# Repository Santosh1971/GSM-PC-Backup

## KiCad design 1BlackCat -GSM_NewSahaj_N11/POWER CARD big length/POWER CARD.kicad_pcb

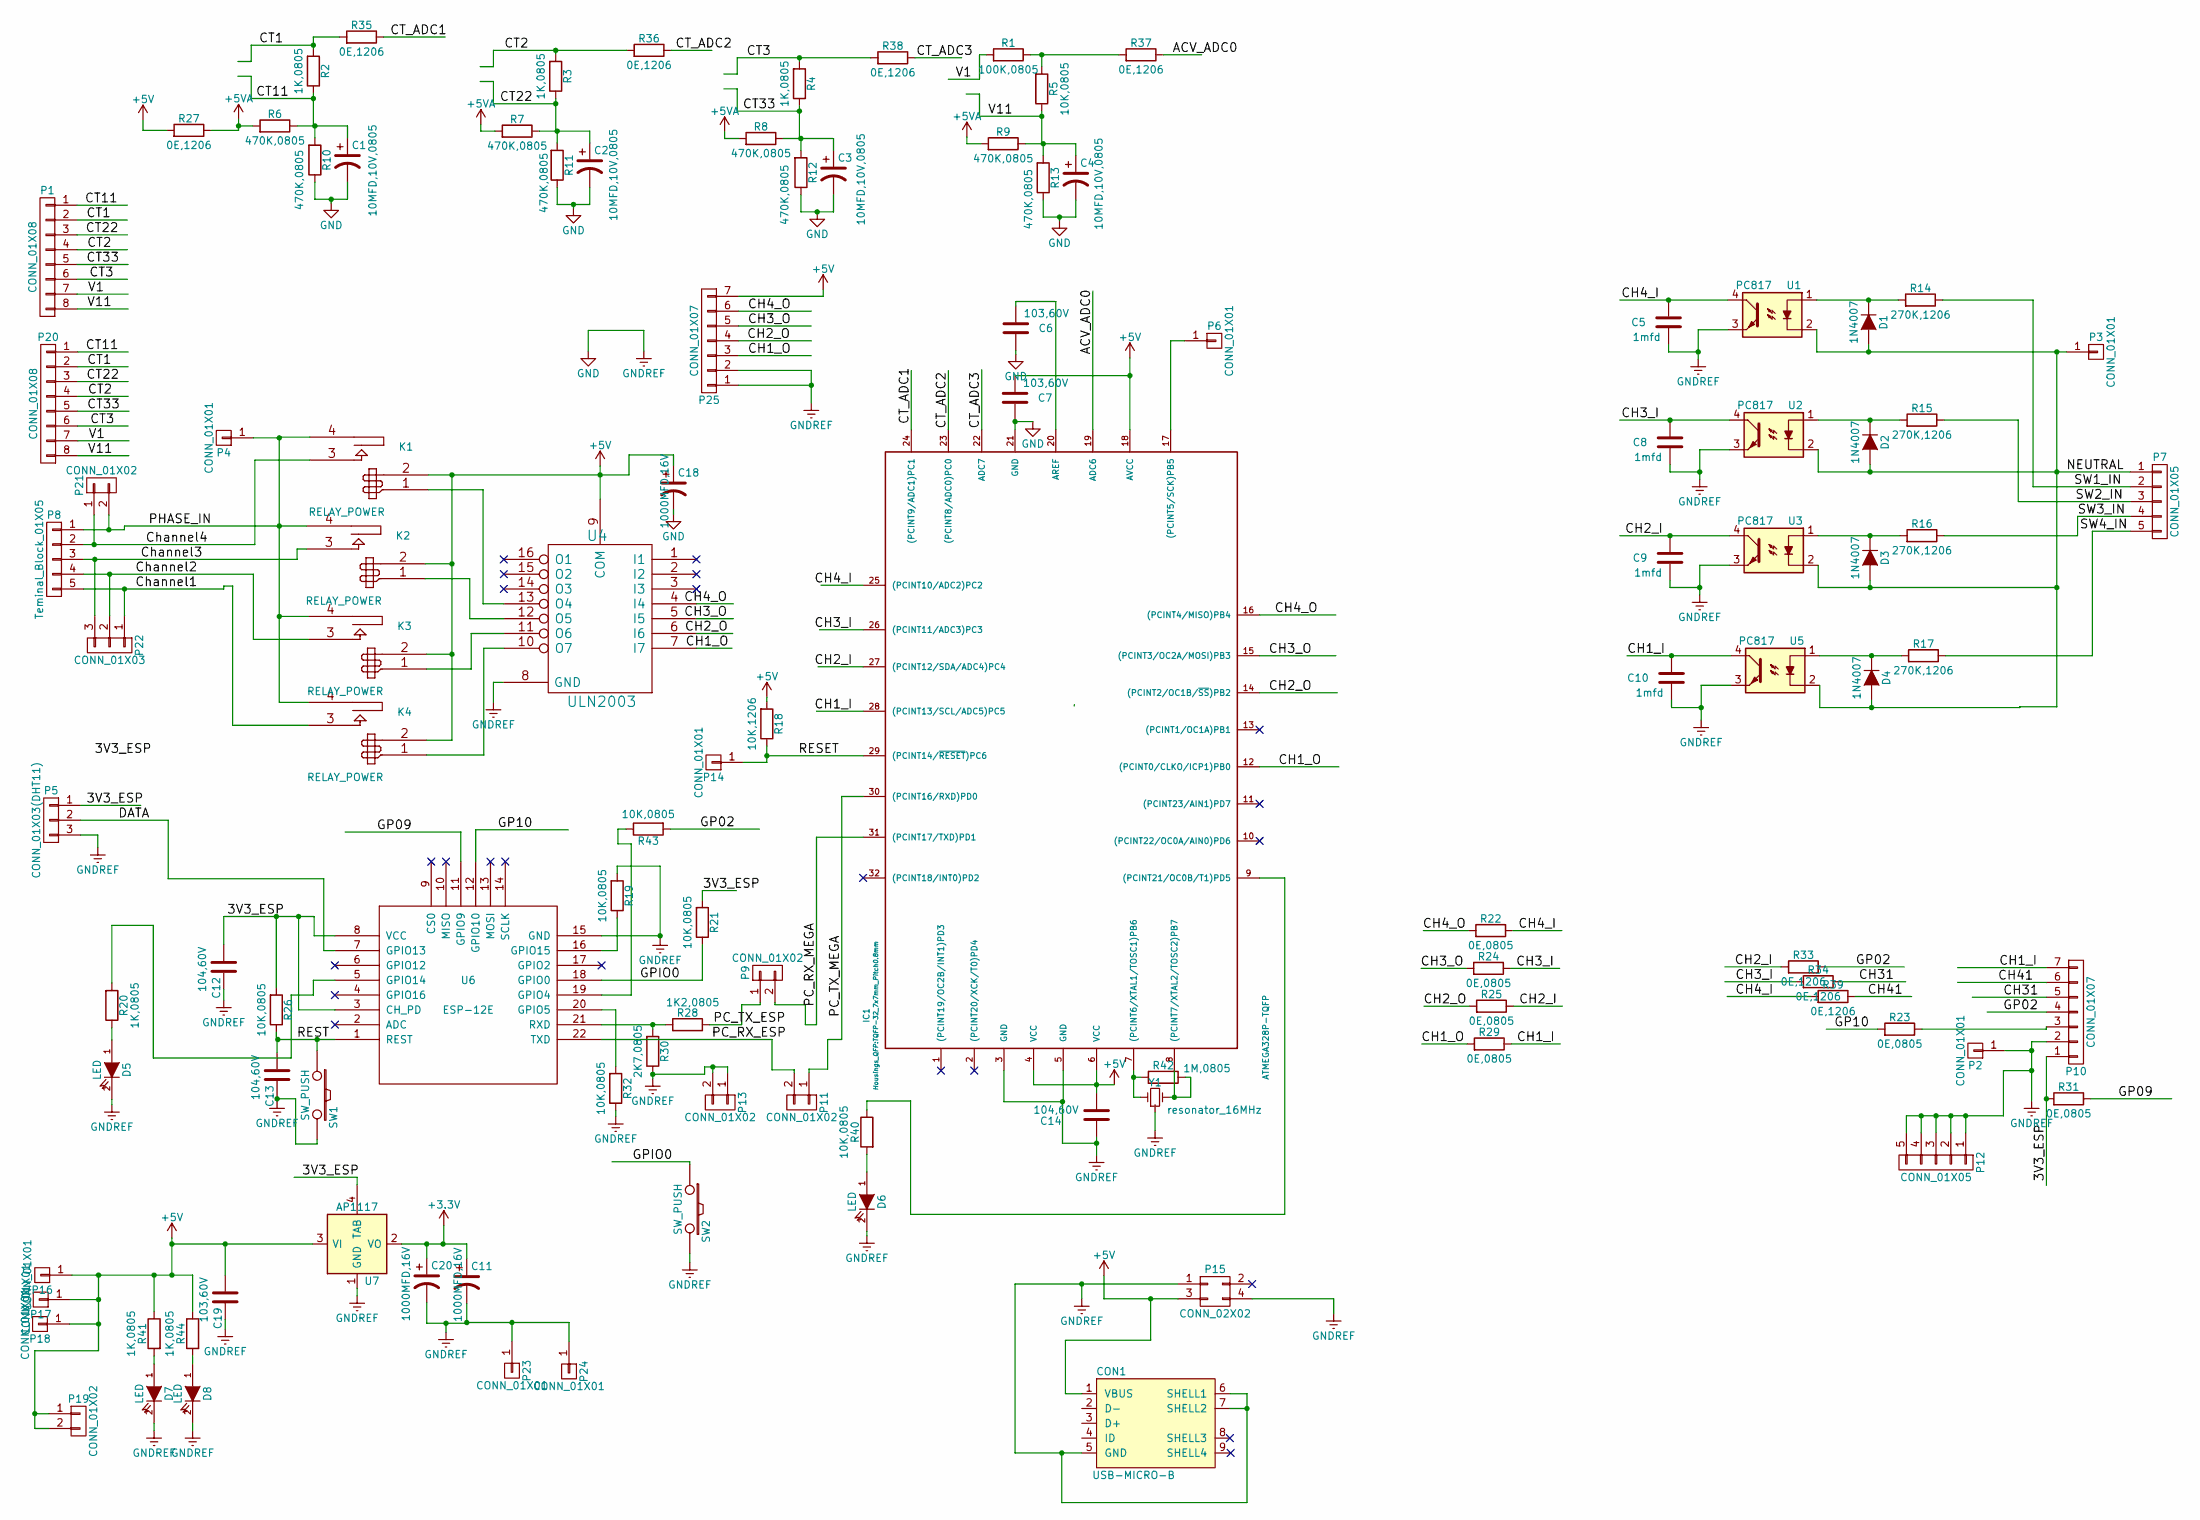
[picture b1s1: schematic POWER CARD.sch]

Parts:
C1, C2, C3, C4: 10MFD,10V,0805; C_0805
C5, C8, C9, C10: 1mfd; C_0805
C6, C19: 103,60V; C_0805
C7: 103,60V; R_0805
C11, C20: 1000MFD,16V; C_Radial_D5_L6_P2.5
C12, C13, C14: 104,60V; C_0805
C18: 1000MFD,16V; C_Radial_D8_L11.5_P3.5
CON1: USB-MICRO-B; USB_Micro-B
D1, D2, D3, D4: 1N4007; SMA_1N4007
D5, D6, D7, D8: LED; LED_0805_ok
IC1: ATMEGA328P-TQFP; TQFP-32_7x7mm_Pitch0.8mm
K1, K2, K3, K4: RELAY_POWER; Relay_KYOTA_KT-594
P1: CONN_01X08; Pin_Header_Straight_1x08
P2: CONN_01X01; Power_card_MegaSize_OK
P3, P4: CONN_01X01; Pin_Header_Straight_1x01
P5: CONN_01X03(DHT11); Pin_Header_Straight_1x03
P6, P14, P16, P17, P18, P23, P24: CONN_01X01; Pin_Header_Straight_1x01_TP_SMD
P7: CONN_01X05; TerminalBlock_WAGO-236_2Stift_RM5mm_5pol
P8: Teminal_Block_01X05; TerminalBlock_WAGO-236_2Stift_RM5mm_5pol_OK
P9, P11, P13, P19: CONN_01X02; Pin_Header_Straight_1x02
P10, P25: CONN_01X07; Pin_Header_Straight_1x07
P12: CONN_01X05; Pin_Header_Straight_1x05
P15: CONN_02X02; Pin_Header_Straight_1x04
P20: CONN_01X08; TerminalBlock_WAGO-236_2Stift_RM5mm_8pol
P21: CONN_01X02; TerminalBlock_WAGO-236_2Stift_RM5mm_2pol
P22: CONN_01X03; TerminalBlock_WAGO-236_2Stift_RM5mm_3pol
R1: 100K,0805; R_0805
R2, R3, R4, R20, R41, R44: 1K,0805; R_0805
R5, R19, R21, R26, R32, R40, R43: 10K,0805; R_0805
R6, R7, R8, R9, R10, R11, R12, R13: 470K,0805; R_0805
R14, R15, R16, R17: 270K,1206; R_1206
R18: 10K,1206; R_1206
R22, R24, R25, R29: 0E,0805; R_0603
R23, R31: 0E,0805; R_0805
R27, R33, R34, R35, R36, R37, R38, R39: 0E,1206; R_1206
R28: 1K2,0805; R_0805
R30: 2K7,0805; R_0805
R42: 1M,0805; R_0805
SW1, SW2: SW_PUSH; SW_SPST_FSMSM
U1, U2, U3, U5: PC817; DIP-4_W7.62mm
U4: ULN2003; SOIC-16_3.9x9.9mm_Pitch1.27mm
U6: ESP-12E
U7: AP1117; SOT-223
Y1: resonator_16MHz; Resonator_16MHz_arduino

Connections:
+3V3: C11.1, C20.1, U7.2 (VO)
+5V: C7.2, C14.2, C18.1, C19.2, CON1.1 (VBUS), IC1.4 (VCC), IC1.6 (VCC), IC1.18 (AVCC), K1.2, K2.2, K3.2, K4.2, P15.3, P16.1, P17.1, P18.1, P19.1, P19.2, P25.7, R18.2, R27.2, R41.1, R44.1, U4.9 (COM), U7.3 (VI); also elsewhere on the board
+5VA: R6.2, R7.2, R8.2, R9.2, R27.1
/3V3_ESP: C12.2, P5.1, P10.1, R21.2, R26.2, R31.2, U6.3 (CH_PD), U6.8 (VCC), U7.4 (TAB)
/ACV_ADC0: IC1.19 (ADC6), R37.1
/CH1_I: C10.1, IC1.28 ((PCINT13/SCL/ADC5)PC5), P10.7, R29.1, U5.4
/CH1_O: IC1.12 ((PCINT0/CLKO/ICP1)PB0), P25.3, R29.2, U4.7 (I7)
/CH2_I: C9.1, IC1.27 ((PCINT12/SDA/ADC4)PC4), R25.1, R33.2, U3.4
/CH2_O: IC1.14 ((PCINT2/OC1B/~SS~)PB2), P25.4, R25.2, U4.6 (I6)
/CH3_I: C8.1, IC1.26 ((PCINT11/ADC3)PC3), R24.1, R34.2, U2.4
/CH3_O: IC1.15 ((PCINT3/OC2A/MOSI)PB3), P25.5, R24.2, U4.5 (I5)
/CH4_I: C5.1, IC1.25 ((PCINT10/ADC2)PC2), R22.1, R39.2, U1.4
/CH4_O: IC1.16 ((PCINT4/MISO)PB4), P25.6, R22.2, U4.4 (I4)
/CH31: P10.5, R34.1
/CH41: P10.6, R39.1
/CT1: P1.2, P20.2, R2.2, R35.2
/CT2: P1.4, P20.4, R3.2, R36.2
/CT3: P1.6, P20.6, R4.2, R38.2
/CT11: C1.1, P1.1, P20.1, R2.1, R6.1, R10.2
/CT22: C2.1, P1.3, P20.3, R3.1, R7.1, R11.2
/CT33: C3.1, P1.5, P20.5, R4.1, R8.1, R12.2
/CT_ADC1: IC1.24 ((PCINT9/ADC1)PC1), R35.1
/CT_ADC2: IC1.23 ((PCINT8/ADC0)PC0), R36.1
/CT_ADC3: IC1.22 (ADC7), R38.1
/Channel1: K4.3, P8.5, P22.1; also elsewhere on the board
/Channel2: K3.3, P8.4, P22.2; also elsewhere on the board
/Channel3: K2.3, P8.3, P22.3; also elsewhere on the board
/Channel4: K1.3, P8.2, P21.1; also elsewhere on the board
/DATA: P5.2, U6.7 (GPIO13)
/GP02: P10.4, R33.1, R43.2
/GP09: R31.1, U6.11 (GPIO9)
/GP10: R23.2, U6.12 (GPIO10)
/GPIO0: R21.1, SW2.1, U6.18 (GPIO0)
/NEUTRAL: D1.1 (A), D2.1 (A), D3.1 (A), D4.1 (A), P3.1, P7.1, U1.2, U2.2, U3.2, U5.2; also elsewhere on the board
/PC_RX_ESP: P11.2, U6.22 (TXD)
/PC_RX_MEGA: IC1.31 ((PCINT17/TXD)PD1), P9.2
/PC_TX_ESP: P9.1, R28.1
/PC_TX_MEGA: IC1.30 ((PCINT16/RXD)PD0), P11.1
/PHASE_IN: K1.4, K2.4, K3.4, K4.4, P4.1, P8.1, P21.2; also elsewhere on the board
/RESET: IC1.29 ((PCINT14/~RESET~)PC6), P14.1, R18.1
/REST: C13.2, R26.1, SW1.1, U6.1 (REST)
/SW1_IN: P7.2, R14.1; also elsewhere on the board
/SW2_IN: P7.3, R15.1; also elsewhere on the board
/SW3_IN: P7.4, R16.1; also elsewhere on the board
/SW4_IN: P7.5, R17.1; also elsewhere on the board
/V1: P1.7, P20.7, R1.2
/V11: C4.1, P1.8, P20.8, R5.1, R9.1, R13.2
GNDREF: C1.2, C2.2, C3.2, C4.2, C5.2, C6.1, C7.1, C8.2, C9.2, C10.2, C11.2, C12.1, C13.1, C14.1, C18.2, C19.1, C20.2, CON1.5 (GND), CON1.6 (SHELL1), CON1.7 (SHELL2), D5.2 (K), D6.2 (K), D7.2 (K), D8.2 (K), IC1.3 (GND), IC1.5 (GND), IC1.21 (GND), P2.1, P5.3, P10.2, P12.1, P12.2, P12.3, P12.4, P12.5, P13.1, P13.2, P15.1, P15.4, P23.1, P24.1, P25.1, P25.2, R10.1, R11.1, R12.1, R13.1, R19.2, R30.1, R32.1, SW1.2, SW2.2, U1.3, U2.3, U3.3, U4.8 (GND), U5.3, U6.15 (GND), U7.1 (GND), Y1.3; also elsewhere on the board
unnamed: C6.2, IC1.20 (AREF)
unnamed: D1.2 (K), R14.2, U1.1
unnamed: D2.2 (K), R15.2, U2.1
unnamed: D3.2 (K), R16.2, U3.1
unnamed: D4.2 (K), R17.2, U5.1
unnamed 53: D5.1 (A), R20.1; also elsewhere on the board
unnamed: D6.1 (A), R40.2
unnamed: D7.1 (A), R41.2
unnamed: D8.1 (A), R44.2
unnamed: IC1.7 ((PCINT6/XTAL1/TOSC1)PB6), R42.2, Y1.1
unnamed: IC1.8 ((PCINT7/XTAL2/TOSC2)PB7), R42.1, Y1.2
unnamed: IC1.9 ((PCINT21/OC0B/T1)PD5), R40.1
unnamed: IC1.17 ((PCINT5/SCK)PB5), P6.1
unnamed: K1.1, U4.13 (O4)
unnamed: K2.1, U4.12 (O5)
unnamed: K3.1, U4.11 (O6)
unnamed: K4.1, U4.10 (O7)
unnamed: P10.3, R23.1
unnamed: R1.1, R5.2, R37.2
unnamed: R19.1, U6.16 (GPIO15)
unnamed: R20.2, U6.5 (GPIO14)
unnamed: R28.2, R30.2, U6.21 (RXD)
unnamed: R32.2, U6.20 (GPIO5)
unnamed: R43.1, U6.19 (GPIO4)

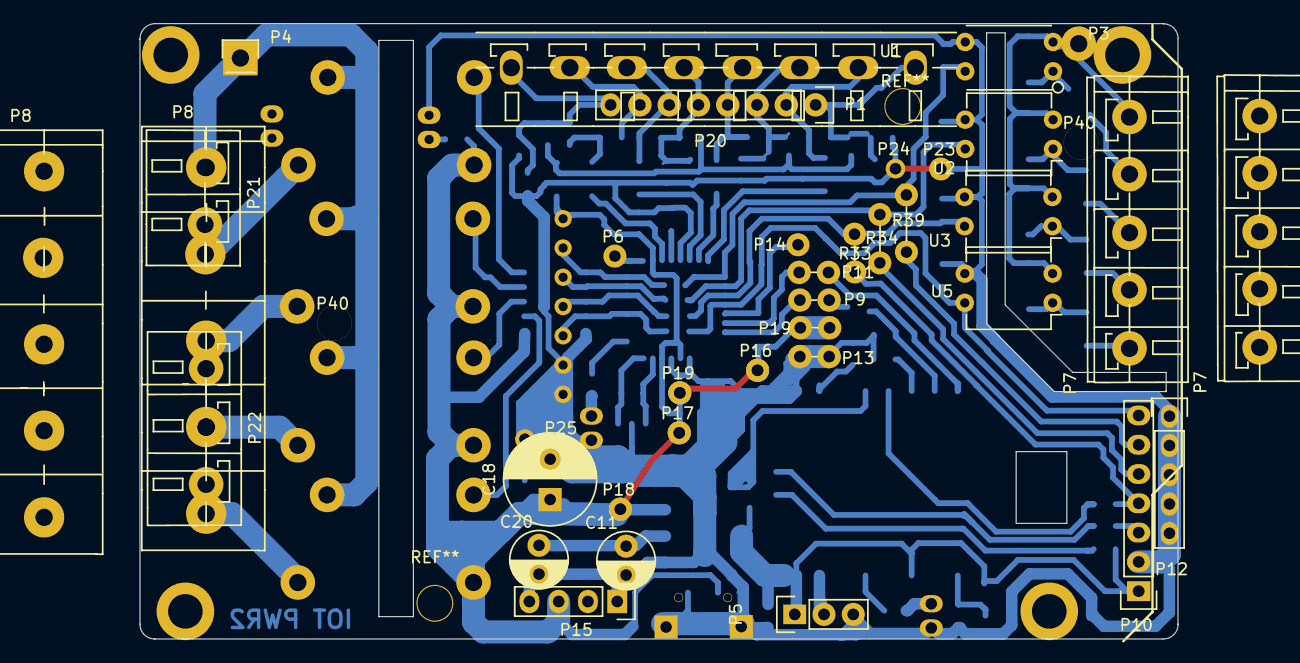
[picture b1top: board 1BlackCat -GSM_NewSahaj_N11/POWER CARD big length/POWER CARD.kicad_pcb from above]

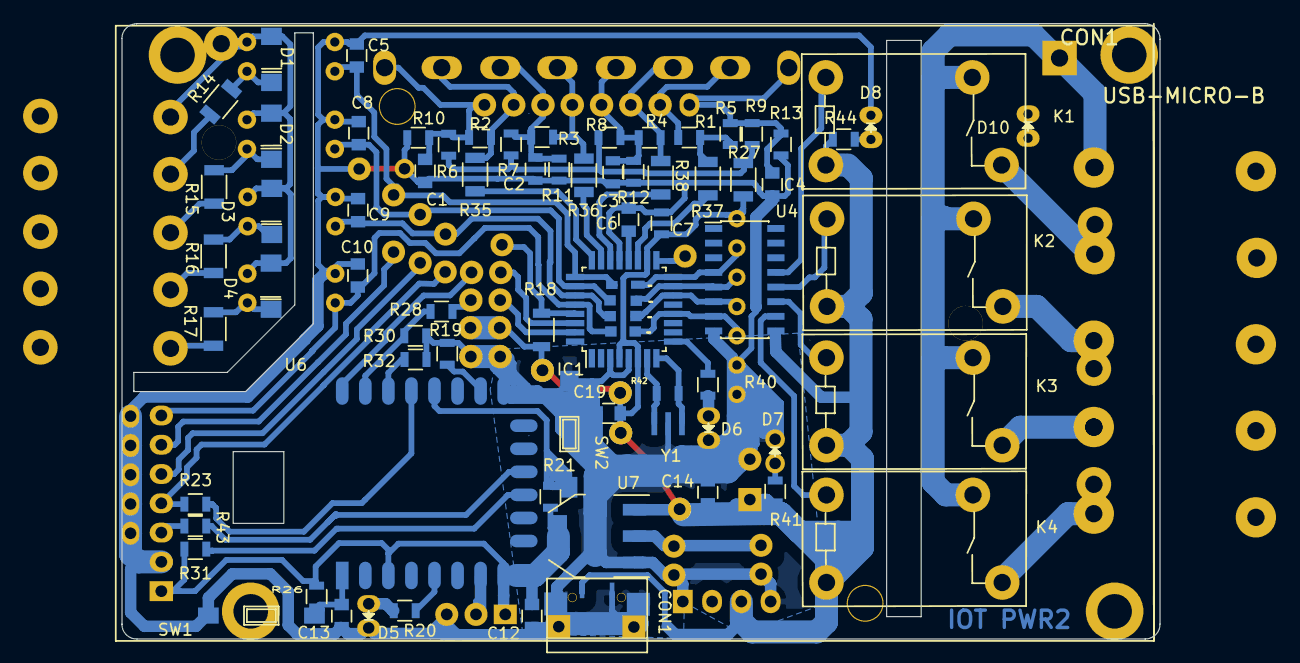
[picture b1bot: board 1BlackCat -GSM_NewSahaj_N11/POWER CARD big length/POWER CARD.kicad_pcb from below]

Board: 2 copper layers, 90.1 x 53.4 mm, 116 parts (77 on the bottom side), 72 nets.

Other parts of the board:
CON1#2: USB-MICRO-B; USB_Micro-B_new
D10: LED; LED_0805_ok
P7#2: CONN_01X05; TerminalBlock_WAGO-236_2Stift_RM5mm_5pol
P8#2: Teminal_Block_01X05; TerminalBlock_WAGO-236_2Stift_RM5mm_5pol_OK
P19#2, P40, P40#2: CONN_01X01; Pin_Header_Straight_1x01_TP_SMD

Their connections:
+5V: P19#2.1; also elsewhere on the board
/Channel1: P8#2.5; also elsewhere on the board
/Channel2: P8#2.4; also elsewhere on the board
/Channel3: P8#2.3; also elsewhere on the board
/Channel4: P8#2.2; also elsewhere on the board
/NEUTRAL: P7#2.1; also elsewhere on the board
/PHASE_IN: P8#2.1; also elsewhere on the board
/SW1_IN: P7#2.2; also elsewhere on the board
/SW2_IN: P7#2.3; also elsewhere on the board
/SW3_IN: P7#2.4; also elsewhere on the board
/SW4_IN: P7#2.5; also elsewhere on the board
GNDREF: D10.2; also elsewhere on the board
unnamed 53: D10.1; also elsewhere on the board

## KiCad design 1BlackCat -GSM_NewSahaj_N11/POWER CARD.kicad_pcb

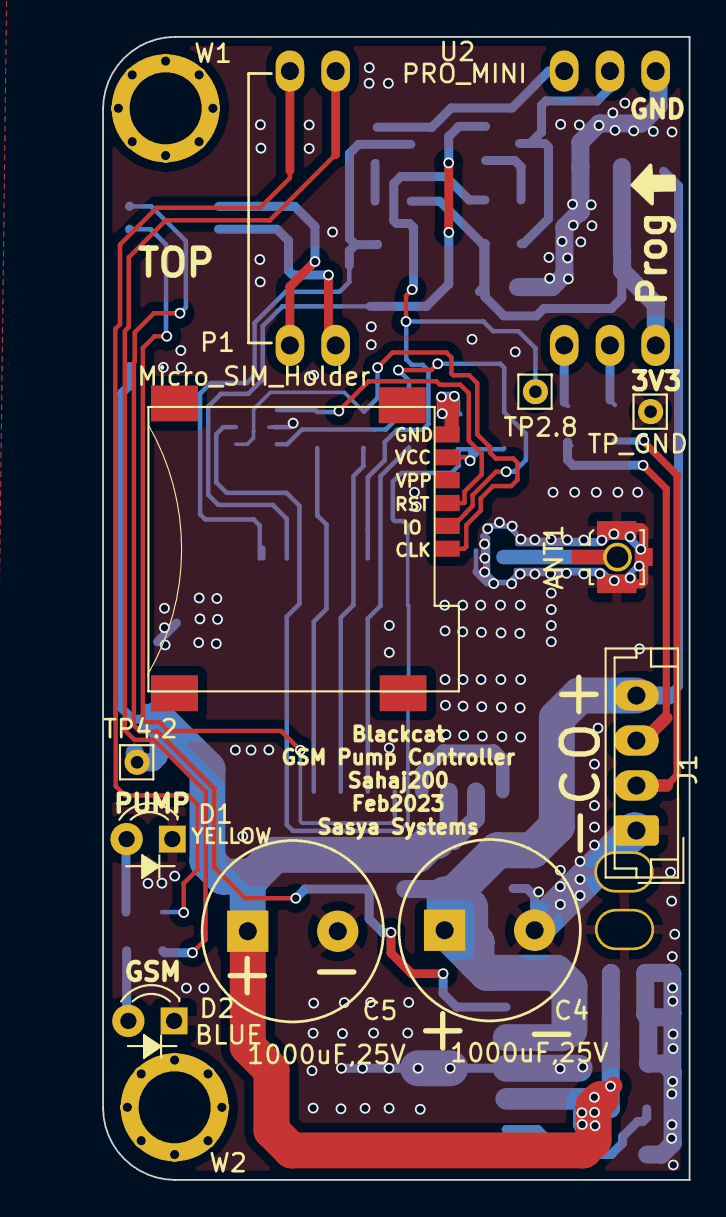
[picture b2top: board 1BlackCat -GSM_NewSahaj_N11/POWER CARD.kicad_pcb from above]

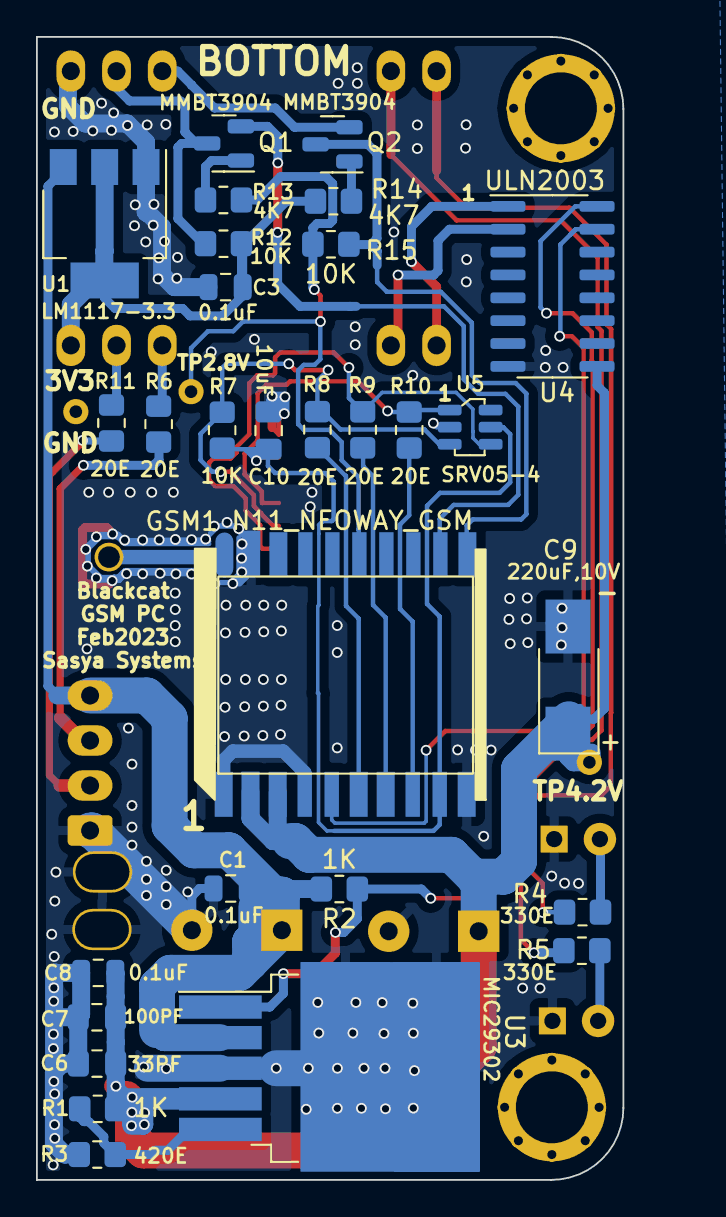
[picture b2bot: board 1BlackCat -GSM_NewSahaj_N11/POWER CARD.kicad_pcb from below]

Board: 2 copper layers, 32.6 x 63.5 mm, 43 parts (29 on the bottom side), 32 nets.

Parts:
AE1: Antenna; SMA_Samtec_SMA-J-P-X-ST-EM1_EdgeMount
ANT1: SMD_ANTENNA; U.FL_Molex_MCRF_73412-0110_Vertical
C1, C3, C8: 0.1uF; C_0805_2012Metric
C4, C5: 1000uF,25V; C_Radial_D10_L16_P5
C6: 33PF; C_0805_2012Metric_Pad1.18x1.45mm_HandSolder
C7: 100PF; C_0805_2012Metric_Pad1.18x1.45mm_HandSolder
C9: 220uF,10V; CP_Tantalum_Case-B_EIA-3528-21_Hand
C10: 10uF; C_0805_2012Metric_Pad1.18x1.45mm_HandSolder
D1: YELLOW; LED_D3.0mm
D2: BLUE; LED_D3.0mm
GSM1: N11_NEOWAY_GSM; N11_LGA20
J1: CONN_04JST-USB; JST_EH_B4B-EH-A_1x04_P2.50mm_Vertical
P1: Micro_SIM_Holder; microSIM_JAE_SF53S006VCBR2000
Q1, Q2: MMBT3904; SOT-23
R1, R2: 1K; R_0805_2012Metric_Pad1.20x1.40mm_HandSolder
R3: 420E; R_0805_2012Metric_Pad1.20x1.40mm_HandSolder
R4, R5: 330E; R_0805_2012Metric_Pad1.20x1.40mm_HandSolder
R6, R8, R9, R10, R11: 20E; R_0805_2012Metric_Pad1.20x1.40mm_HandSolder
R7, R12, R15: 10K; R_0805_2012Metric_Pad1.20x1.40mm_HandSolder
R13, R14: 4K7; R_0805_2012Metric_Pad1.20x1.40mm_HandSolder
TP1: TP4.2; Pin_D0.7mm_L6.5mm_W1.8mm_FlatFork
TP2: TP2.8; Pin_D0.7mm_L6.5mm_W1.8mm_FlatFork
TP3: TP_GND; Pin_D0.7mm_L6.5mm_W1.8mm_FlatFork
U1: LM1117-3.3; SOT-223-3_TabPin2
U2: PRO_MINI; DIP-24_W15.24mm_LongPad_Pro_Mini
U3: MIC29302; TO-263-5_TabPin3
U4: ULN2003; SOIC-16_3.9x9.9mm_P1.27mm
U5: SRV05-4; SOT-23-6
W1, W2: M_Hole; MountingHole_3.5mm_Pad_Via

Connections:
3.3V: C3.1, R12.1, R14.1, U1.2 (VO), U2.21 (VCC)
/BLUE_LED_GSM-STATUS: R5.2, U2.11 (8)
/GSM_ON: GSM1.5 (ON/OFF), U4.15 (O2)
/GSM_ON/OFF: U2.14 (D11_MOSI), U4.2 (I2)
/GSM_SD: R2.1, U3.1 (~SHDN), U4.16 (O1)
/GSM_SHUTDOWN: U2.13 (D10_SS), U4.1 (I1)
/MCU_Rx: Q1.3 (C), R12.2, U2.5 (2)
/MCU_Tx: Q2.2 (E), U2.6 (3)
/Module_Rx: GSM1.11 (UART_RXD), Q2.3 (C), R15.2
/Module_Tx: GSM1.12 (UART_TXD), Q1.2 (E)
/RLY_NC: J1.2, R11.2
/RLY_NO: J1.3, R6.2
/SIM_CLK: P1.CLK, R9.1, U5.4 (IO3)
/SIM_IO: P1.I/O, R7.2, R8.1, U5.3 (IO2)
/SIM_RST: P1.RST, R10.1, U5.1 (IO1)
/VDDIO_2P8: GSM1.15 (VDDIO_2P8), R13.1, R15.1, TP2.1
/VSIM: C10.1, GSM1.9 (VSIM), P1.VCC, R7.1, U5.5 (VP)
/V_IN: C1.1, C4.1, J1.4, R2.2, U1.3 (VI), U3.2 (VIN)
/YELLOW_LED_PUMP: R4.2, U2.12 (9)
GND: ANT1.2, C1.2, C3.2, C4.2, C5.2, C6.2, C7.2, C8.2, C9.2, C10.2, D1.1 (K), D2.1 (K), GSM1.1 (GND), GSM1.4 (GND), GSM1.10 (GND), GSM1.19 (GND), J1.1, P1.GND, R3.2, TP3.1, U1.1 (GND), U2.4 (GND), U3.3 (GND), U4.8 (GND), U5.2 (VN)
unnamed: AE1.1 (A), ANT1.1, GSM1.20 (ANT)
unnamed: D1.2 (A), R4.1
unnamed: D2.2 (A), R5.1
unnamed: GSM1.6 (SIM_DATA), R8.2
unnamed: GSM1.7 (SIM_CLK), R9.2
unnamed: GSM1.8 (SIM_RESET), R10.2
unnamed: Q1.1 (B), R13.2
unnamed: Q2.1 (B), R14.2
unnamed: R1.1, R3.1, U3.5 (ADJ)
unnamed: R6.1, U2.19 (A2)
unnamed: R11.1, U2.20 (A3)
VDD: C5.1, C6.1, C7.1, C8.1, C9.1, GSM1.2 (VBAT), GSM1.3 (VBAT), R1.2, TP1.1, U3.4 (OUT), U4.9 (COM)

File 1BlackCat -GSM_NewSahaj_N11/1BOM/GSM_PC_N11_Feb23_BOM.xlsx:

Id | Designator | Qnty | Designation | Cost | Supplier and ref | Column1 | _1
1 | U1 | 1 | SMD Regulator ,LM1117-3.3, SOT 223-3 | 10 | Namotronics, SP Road Bangalore
2 | U2 | 1 | PRO_MINI | 250 | OM Technology,SP Road Bangalore
3 | U3 | 1 | SMD Regulator , MIC29302 , TO-263-5 | 135 | Namotronics, SP Road Bangalore
4 | U4 | 1 | ULN2003 , SMD( SOIC -16) | 12 | Namotronics, SP Road Bangalore
5 | U5 | 1 | SRV05-4 , SMD( SOT-23-6)
6 | GSM1 | 1 | N11_NEOWAY_GSM **** From Dealer | 250 | Rashi Peripherals Limited(RP Tech)/Online
7 | Q2,Q1 | 2 | SMD Transistor ,MMBT3904 ,SOT-23 | 1.25 | Namotronics, SP Road Bangalore
8 | D1 | 1 | 3mm YELLOW LED | 0.8 | OM Technology,SP Road Bangalore
9 | D2 | 1 | 3mm BLUE LED | 0.8 | OM Technology,SP Road Bangalore
10 | P1 | 1 | Micro_SIM_Holder | 55 | Nihartronics,SP Road Bangalore | https://www.ktron.in/product/micro-sim-card-holder-smd/?utm_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
11 | R1,R2 | 2 | 1K ,0805 | 0.2 | Namotronics, SP Road Bangalore
12 | R3 | 1 | 420E,0805 | 0.2 | Namotronics, SP Road Bangalore
13 | R5,R4 | 2 | 330E ,0805 | 0.2 | Namotronics, SP Road Bangalore
14 | R10,R6,R8,R9,R11 | 5 | 20E,0805 | 0.2 | Namotronics, SP Road Bangalore
15 | R7,R15,R12 | 3 | 10K,0805 | 0.2 | Namotronics, SP Road Bangalore
16 | R14,R13 | 2 | 4K7 ,0805 | 0.2 | Namotronics, SP Road Bangalore
17 | C3,C1,C8 | 3 | 0.1uF,0805 | 1 | Namotronics, SP Road Bangalore
18 | C5,C4 | 2 | 1000uF,25V, TH | 4.5 | OM Technology,SP Road Bangalore
19 | C6 | 1 | 33PF ,0805 | 0.8 | Namotronics, SP Road Bangalore
20 | C7 | 1 | 100PF ,0805 | 0.8 | Namotronics, SP Road Bangalore
21 | C9 | 1 | SMD Tentalum , 220uF,10V | 13 | Namotronics, SP Road Bangalore
22 | C10 | 1 | 10uF,0805 | 1.5 | Namotronics, SP Road Bangalore
23 | W2,W1 | 2 | Screws Self threaded -small | 0.14000000000000001 | Durga Trading Company,SP Road Bangalore
24 | ANT1 | 1 | Spring ANTENNA / Small Antenna | 8 | Nihartronics,SP Road Bangalore
25 | J1 | 1 | 4 Pin JST connector *** Not Required
26 |  | 4 | Screw for Enclouser | 0.2 | Durga Trading Company,SP Road Bangalore
27 |  | 1 | Black cat Enclouser | 85 | RAJ ENGG. BANGALORE
28 |  | 1 | usb cable | 35 | OM Technology,SP Road Bangalore
29 |  | 1 | PCB | 100 | CIRCUIT SYSTEM INDIA LTD. GUJARAT.
30 |  | 1 | 440V to 5V PowerSupply | 371
 |  |  | TOTAL | 1336.9900000000002

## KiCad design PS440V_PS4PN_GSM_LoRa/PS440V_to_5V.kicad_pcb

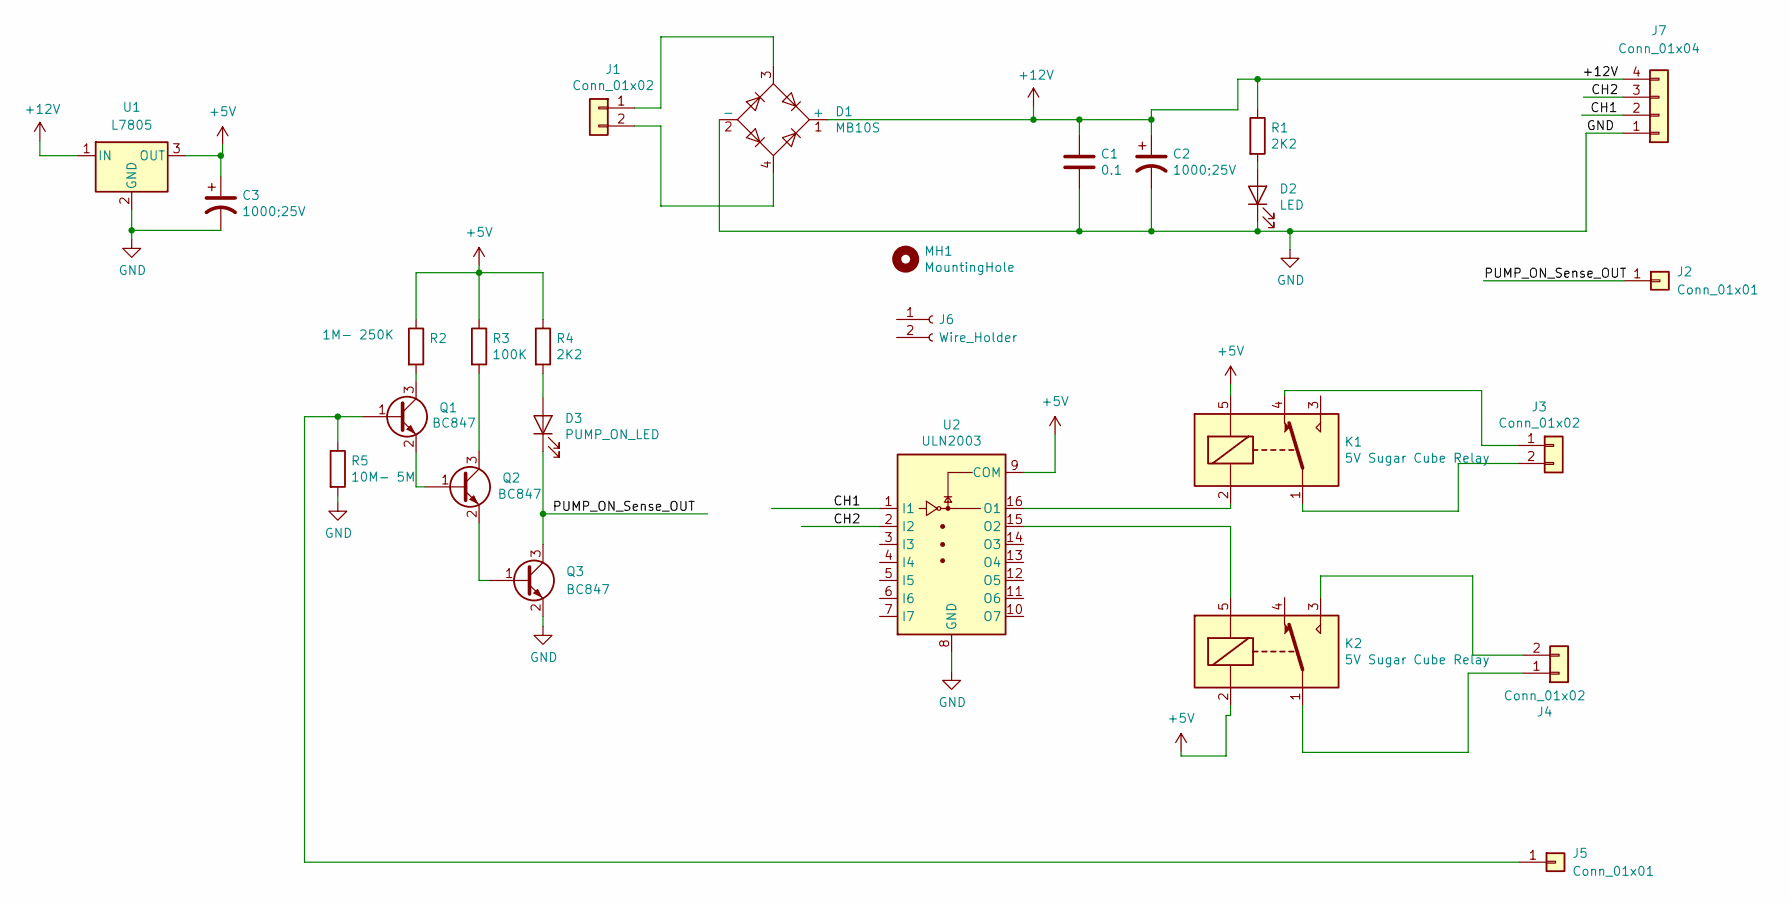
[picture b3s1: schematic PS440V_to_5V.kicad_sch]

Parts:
C1: 0.1; C_0805_2012Metric
C2, C3: 1000;25V; C_Radial_D10.0mm_H12.5mm_P5.00mm
D1: MB10S; SOP-4_3.8x4.1mm_Pitch2.54mm
D2: LED; LED_D5.0mm
D3: PUMP_ON_LED; LED_D5.0mm
J1, J3, J4: Conn_01x02; PinHeader_1x02_P2.54mm_Vertical
J2, J5: Conn_01x01; Pin_D1.0mm_L10.0mm
J6: Wire_Holder; PinSocket_1x02_P2.54mm_Vertical
J7: Conn_01x04; JST_EH_B4B-EH-A_1x04_P2.50mm_Vertical
K1, K2: 5V Sugar Cube Relay; Relay_SPDT_SANYOU_SRD_Series_Form_C
MH1: MountingHole; MountingHole_2.2mm_M2_Pad
Q1, Q2, Q3: BC847; SOT-23
R1, R4: 2K2; R_0805_2012Metric
R2: 1M- 250K; R_0805_2012Metric
R3: 100K; R_0805_2012Metric
R5: 10M- 5M; R_0805_2012Metric
U1: L7805; TO-252-2
U2: ULN2003; SOIC-16W_5.3x10.2mm_P1.27mm

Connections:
+5V: C3.1, K1.5, K2.2, R2.1, R3.1, R4.1, U1.3 (OUT), U2.9 (COM)
+12V: C1.1, C2.1, D1.1 (+), J7.4, R1.1, U1.1 (IN)
/CH1: J7.2, U2.1 (I1)
/CH2: J7.3, U2.2 (I2)
/PUMP_ON_Sense_OUT: D3.1 (K), J2.1, Q3.3 (C)
GND: C1.2, C2.2, C3.2, D1.2 (-), D2.1 (K), J7.1, Q3.2 (E), R5.2, U1.2 (GND), U2.8 (GND)
unnamed: D1.3, J1.1
unnamed: D1.4, J1.2
unnamed: D2.2 (A), R1.2
unnamed: D3.2 (A), R4.2
unnamed: J3.1, K1.4
unnamed: J3.2, K1.1
unnamed: J4.1, K2.1
unnamed: J4.2, K2.3
unnamed: J5.1, Q1.1 (B), R5.1
unnamed: K1.2, U2.16 (O1)
unnamed: K2.5, U2.15 (O2)
unnamed: Q1.2 (E), Q2.1 (B)
unnamed: Q1.3 (C), R2.2
unnamed: Q2.2 (E), Q3.1 (B)
unnamed: Q2.3 (C), R3.2

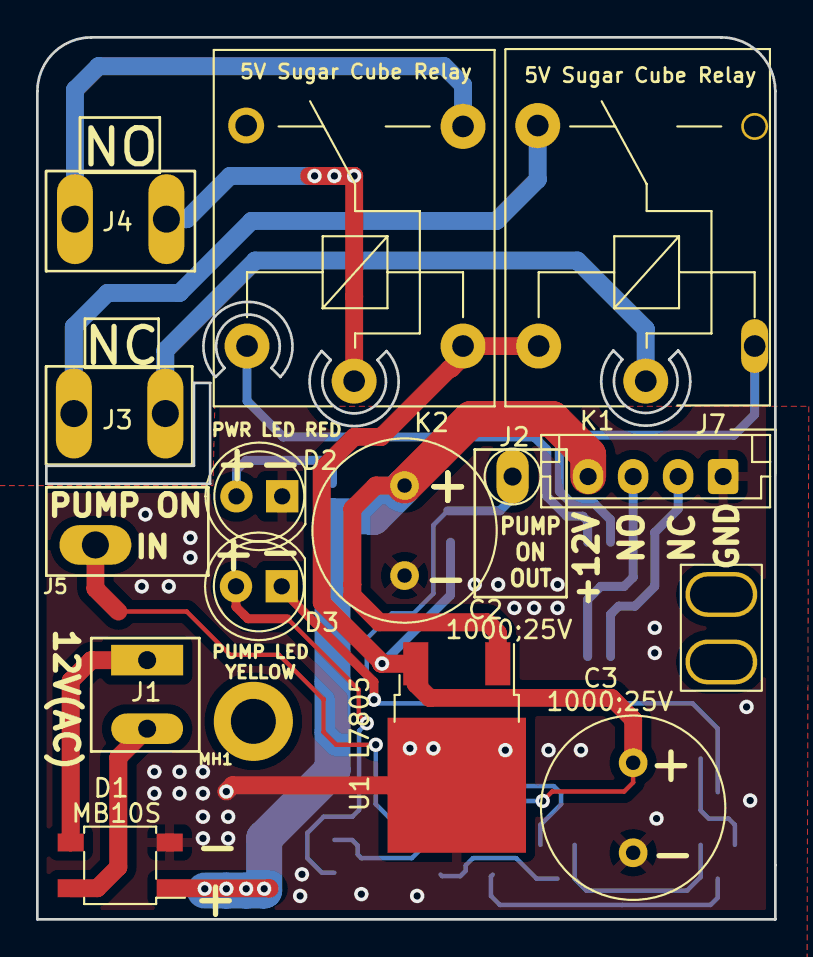
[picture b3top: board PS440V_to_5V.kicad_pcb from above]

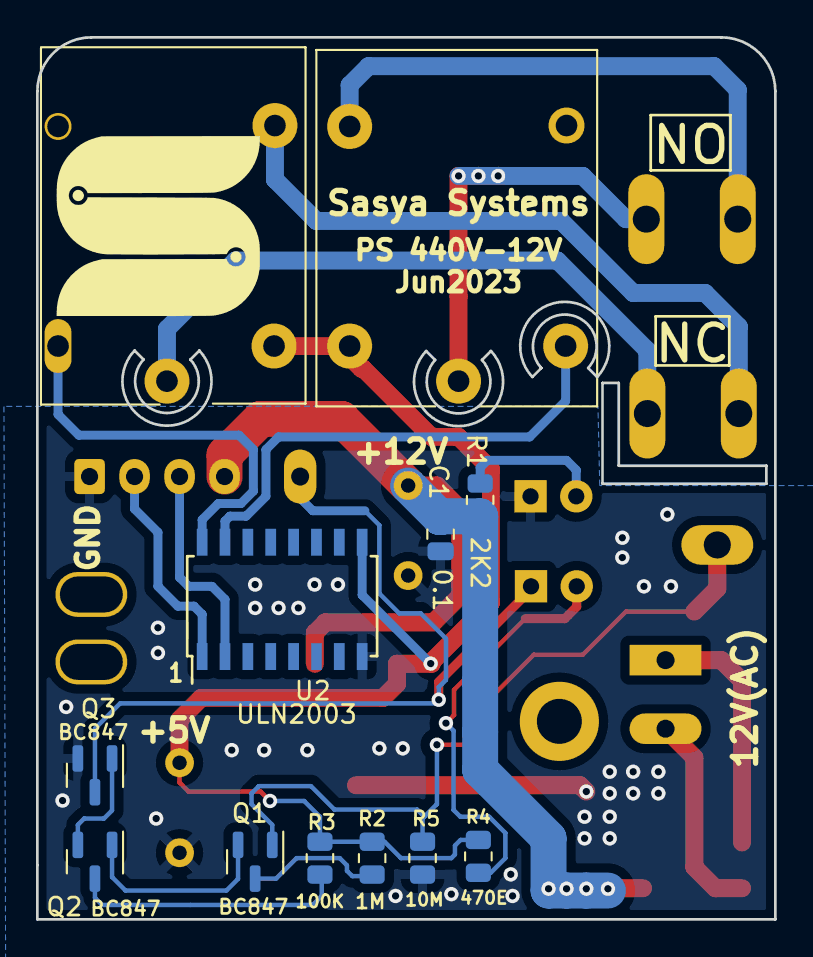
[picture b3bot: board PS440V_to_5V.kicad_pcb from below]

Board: 2 copper layers, 41.0 x 49.0 mm, 26 parts (10 on the bottom side), 21 nets.

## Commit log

2025-12-24 Inditial backup
2025-12-24 added N11 PCB
